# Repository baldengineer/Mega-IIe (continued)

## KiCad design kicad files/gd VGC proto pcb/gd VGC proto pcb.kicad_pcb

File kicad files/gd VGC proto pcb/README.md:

## gd VGC proto pcb
VGC = Video Graphics Controller

First board to be finished and the one with the least use for the final handheld. The VGC converts the RGB bitstream from the MEGA-II into an analog signal and then into NTSC.

The VGC also generates the 14 MHz clock from a 28 MHz oscilliator. (It is not clear yet which clocks the MEGA-II generates and which the VGC does.)

Runs off of +5V, -5V, and +12V. The 12V and -5V are used by the NTSC generation circuit.

## Rev1 Notes:
* Nothing... yet :)

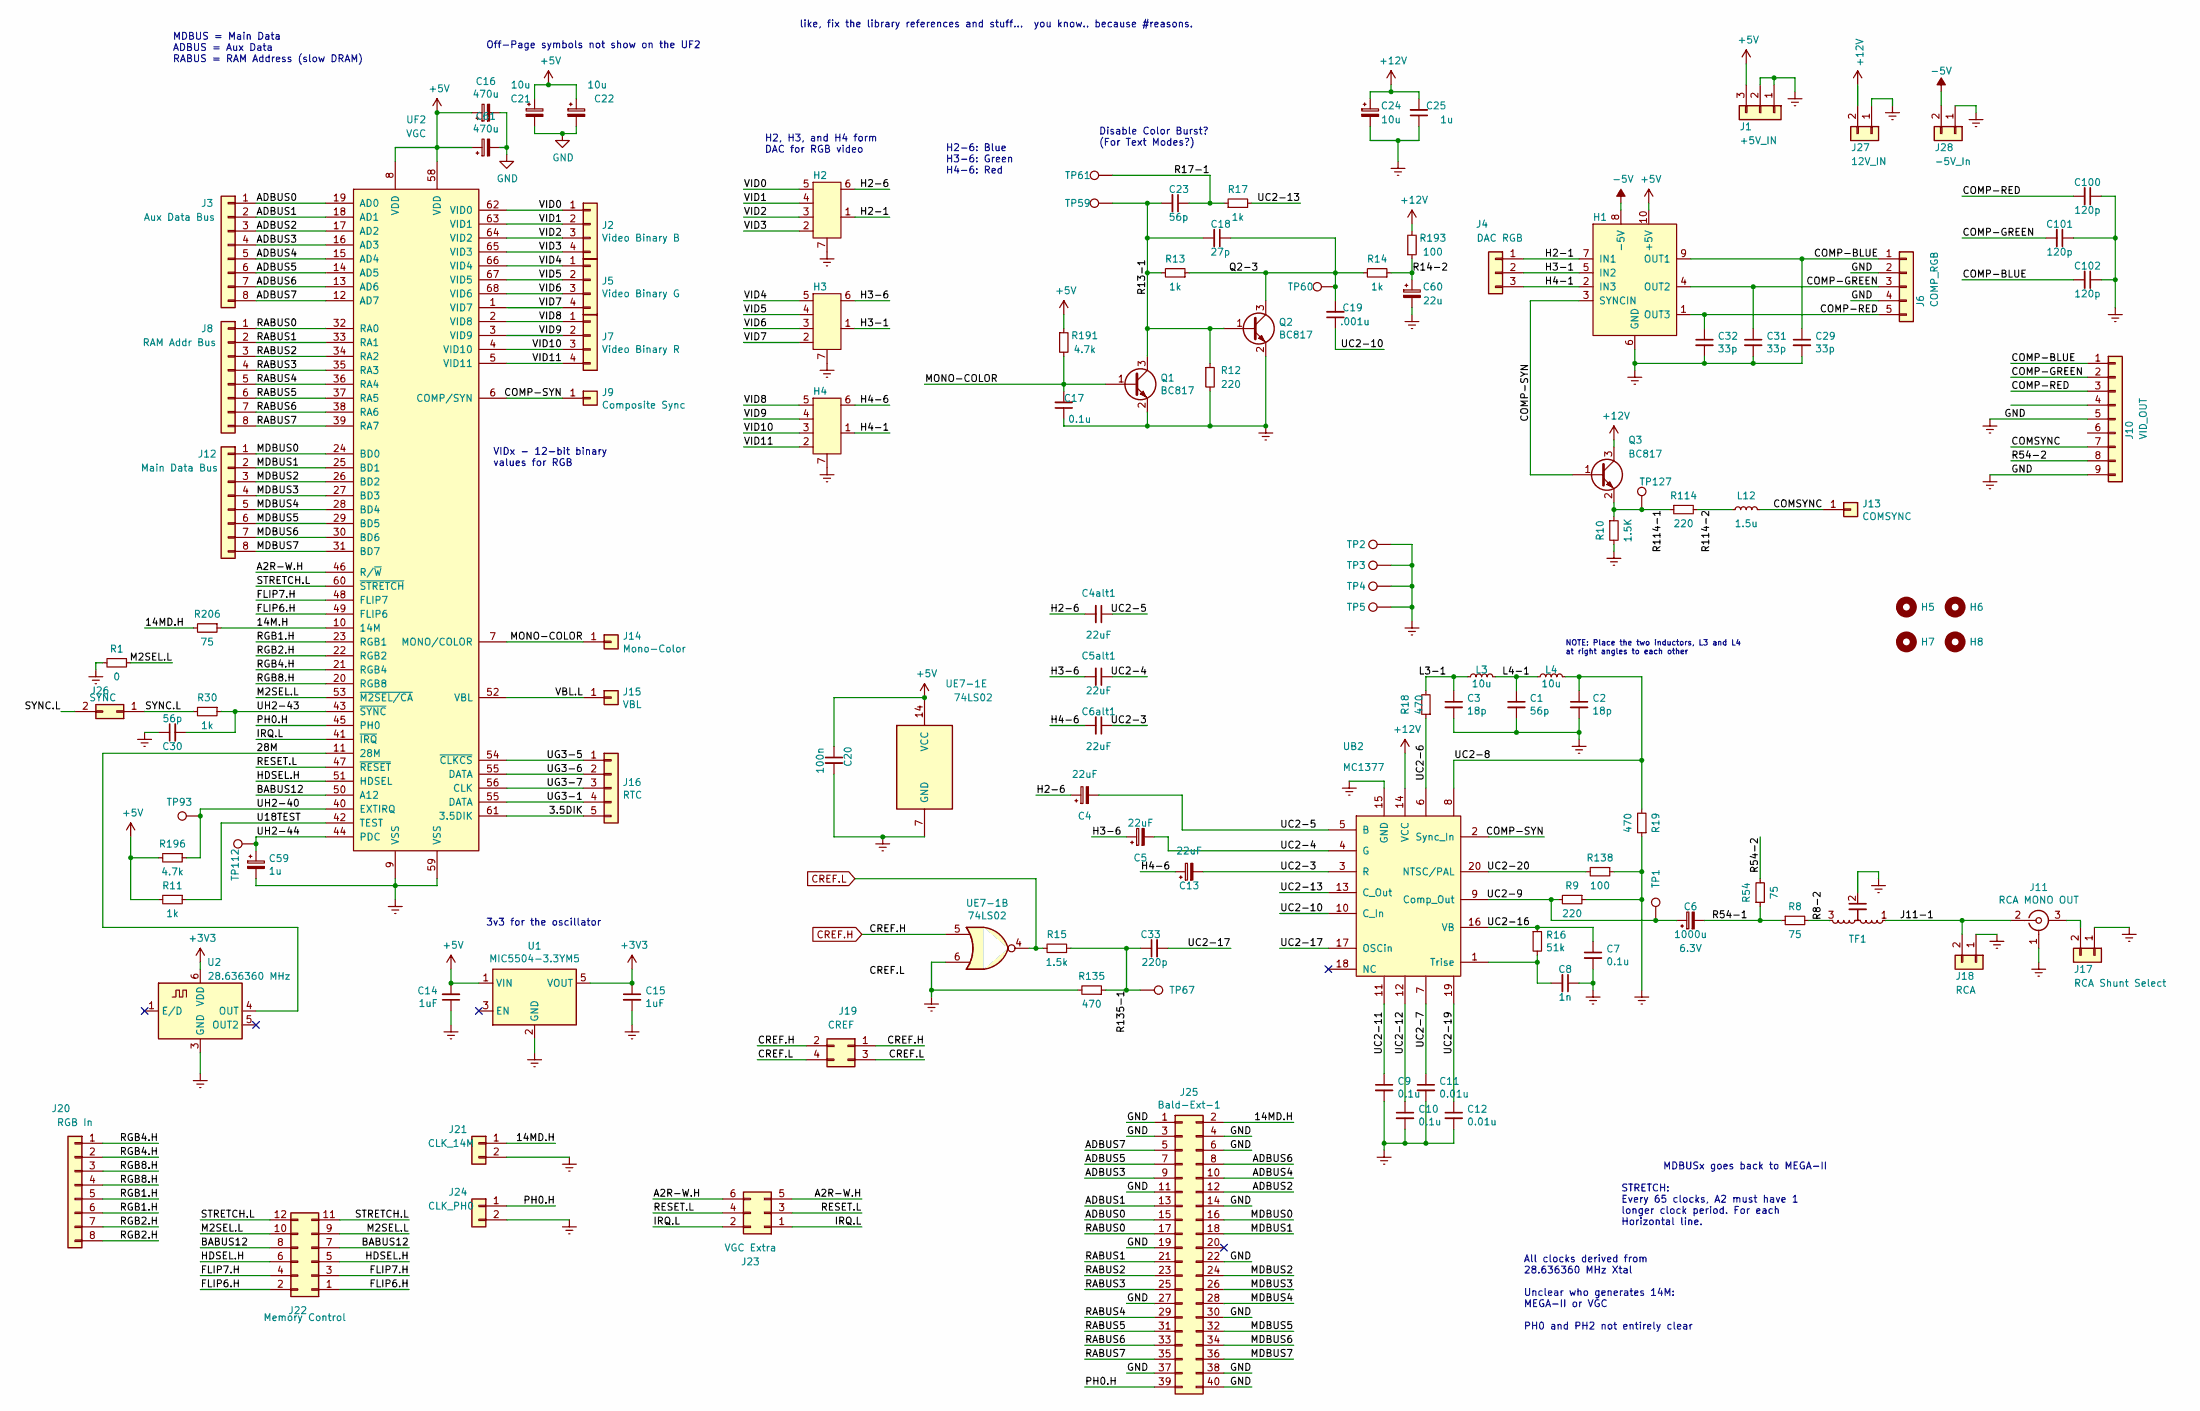
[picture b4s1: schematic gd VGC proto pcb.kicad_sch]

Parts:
C1, C23, C30: 56p; C_0805_2012Metric
C2, C3: 18p; C_0805_2012Metric
C4, C5, C13: 22uF; CP_Radial_D5.0mm_P2.00mm
C4alt1, C5alt1, C6alt1: 22uF; C_0805_2012Metric
C6: 1000u; CP_Radial_D10.0mm_P2.50mm; Voltage 6.3V
C7, C9, C10, C17: 0.1u; C_0805_2012Metric
C8: 1n; C_0805_2012Metric
C11, C12: 0.01u; C_0805_2012Metric
C14, C15: 1uF; C_0805_2012Metric
C16, C61: 470u; CP_Radial_D10.0mm_P2.50mm
C18: 27p; C_0805_2012Metric
C19: .001u; C_0805_2012Metric
C20: 100n; C_0805_2012Metric
C21, C22, C24: 10u; CP_Radial_D5.0mm_P2.50mm
C25, C59: 1u; C_0805_2012Metric
C29, C31, C32: 33p; C_0805_2012Metric
C33: 220p; C_0805_2012Metric
C60: 22u; CP_Radial_D5.0mm_P2.50mm
C100, C101, C102: 120p; C_0805_2012Metric
H1: Video_Sync; R_Array_SIP10
H2, H3, H4: VideoThingy; R_Array_SIP7
H5, H6, H7, H8: MountingHole; MountingHole_2.7mm_M2.5
J1: +5V_IN; PinHeader_1x03_P2.54mm_Vertical
J2: Video Binary B; PinHeader_1x04_P2.54mm_Vertical
J3: Aux Data Bus; PinHeader_1x08_P2.54mm_Vertical
J4: DAC RGB; PinHeader_1x03_P2.54mm_Vertical
J5: Video Binary G; PinHeader_1x04_P2.54mm_Vertical
J6: COMP_RGB; PinHeader_1x05_P2.54mm_Vertical
J7: Video Binary R; PinHeader_1x04_P2.54mm_Vertical
J8: RAM Addr Bus; PinHeader_1x08_P2.54mm_Vertical
J9: Composite Sync; PinHeader_1x01_P2.54mm_Vertical
J10: VID_OUT; PinHeader_1x09_P2.54mm_Vertical
J11: RCA MONO OUT; Jack_RCA_Switchcraft_PJRAN1X1UxxX; MPN PJRAN1X1U02AUX
J12: Main Data Bus; PinHeader_1x08_P2.54mm_Vertical
J13: COMSYNC; PinHeader_1x01_P2.54mm_Vertical
J14: Mono-Color; PinHeader_1x01_P2.54mm_Vertical
J15: VBL; PinHeader_1x01_P2.54mm_Vertical
J16: RTC; PinHeader_1x05_P2.54mm_Vertical
J17: RCA Shunt Select; PinHeader_1x02_P2.54mm_Vertical
J18: RCA; PinHeader_1x02_P2.54mm_Vertical
J19: CREF; PinHeader_2x02_P2.54mm_Vertical
J20: RGB In; PinHeader_1x08_P2.54mm_Vertical
J21: CLK_14M; PinHeader_1x02_P2.54mm_Vertical
J22: Memory Control; PinHeader_2x06_P2.54mm_Vertical
J23: VGC Extra; PinHeader_2x03_P2.54mm_Vertical
J24: CLK_PH0; PinHeader_1x02_P2.54mm_Vertical
J25: Bald-Ext-1; PinHeader_2x20_P2.54mm_Vertical
J26: SYNC; PinHeader_1x02_P2.54mm_Vertical
J27: 12V_IN; PinHeader_1x02_P2.54mm_Vertical
J28: -5V_In; PinHeader_1x02_P2.54mm_Vertical
L3, L4: 10u; L_Axial_L6.6mm_D2.7mm_P10.16mm_Horizontal_Vishay_IM-2
L12: 1.5u; L_Axial_L6.6mm_D2.7mm_P10.16mm_Horizontal_Vishay_IM-2
Q1, Q2, Q3: BC817; SOT-23
R1: 0; R_0805_2012Metric
R8, R54, R206: 75; R_0805_2012Metric
R9, R12, R114: 220; R_0805_2012Metric
R10: 1.5K; R_0805_2012Metric
R11, R13, R14, R17, R30: 1k; R_0805_2012Metric
R15: 1.5k; R_0805_2012Metric
R16: 51k; R_0805_2012Metric
R18, R19, R135: 470; R_0805_2012Metric
R138, R193: 100; R_0805_2012Metric
R191, R196: 4.7k; R_0805_2012Metric
TF1: CapacitiveTransformer; TO-92
TP1, TP2, TP3, TP4, TP5, TP59, TP60, TP61, TP67, TP93, TP112, TP127: TestPoint; Harwin-S1751-46-Test-Point
U1: MIC5504-3.3YM5; SOT-23-5
U2: 28.636360 MHz; Oscillator_SMD_IDT_JU6-6_7.0x5.0mm_P2.54mm
UB2: MC1377; DIP-20_W7.62mm_Socket
UE7-1: 74LS02; SOIC-14_3.9x8.7mm_P1.27mm
UF2: VGC; PLCC-68_THT-Socket

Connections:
+3V3: C15.1, U1.5 (VOUT), U2.6 (VDD)
+5V: C14.2, C16.1, C20.1, C21.1, C22.1, C61.1, H1.10 (+5V), J1.3, R11.2, R191.1, R196.2, U1.1 (VIN), UE7-1.14 (VCC), UF2.8 (VDD), UF2.58 (VDD)
+12V: C24.1, C25.2, J27.2, Q3.3 (C), R193.2, UB2.14 (VCC)
-5V: H1.8 (-5V), J28.2
/3.5DIK: J16.5, UF2.61 (3.5DIK)
/14M.H: R206.1, UF2.10 (14M)
/14MD.H: J21.1, J25.2, R206.2
/28M: U2.4 (OUT), UF2.11 (28M)
/A2R-W.H: J23.5, J23.6, UF2.46 (R/~W)
/ADBUS0: J3.1, J25.15, UF2.19 (AD0)
/ADBUS1: J3.2, J25.13, UF2.18 (AD1)
/ADBUS2: J3.3, J25.12, UF2.17 (AD2)
/ADBUS3: J3.4, J25.9, UF2.16 (AD3)
/ADBUS4: J3.5, J25.10, UF2.15 (AD4)
/ADBUS5: J3.6, J25.7, UF2.14 (AD5)
/ADBUS6: J3.7, J25.8, UF2.13 (AD6)
/ADBUS7: J3.8, J25.5, UF2.12 (AD7)
/BABUS12: J22.7, J22.8, UF2.50 (A12)
/COMP-BLUE: C29.1, C102.2, H1.9 (OUT1), J6.1, J10.1
/COMP-GREEN: C31.1, C101.2, H1.4 (OUT2), J6.3, J10.2
/COMP-RED: C32.1, C100.2, H1.1 (OUT3), J6.5, J10.3
/COMP-SYN: H1.3 (SYNCIN), J9.1, Q3.1 (B), UB2.2 (Sync_In), UF2.6 (COMP/SYN)
/COMSYNC: J10.7, J13.1, L12.2
/FLIP6.H: J22.1, J22.2, UF2.49 (FLIP6)
/FLIP7.H: J22.3, J22.4, UF2.48 (FLIP7)
/H2-1: H1.7 (IN1), H2.1, J4.1
/H2-6: C4.1, C4alt1.2, H2.6
/H3-1: H1.5 (IN2), H3.1, J4.2
/H3-6: C5.1, C5alt1.2, H3.6
/H4-1: H1.2 (IN3), H4.1, J4.3
/H4-6: C6alt1.2, C13.1, H4.6
/HDSEL.H: J22.5, J22.6, UF2.51 (HDSEL)
/IRQ.L: J23.1, J23.2, UF2.41 (~IRQ)
/J11-1: J11.2 (In), J18.2, TF1.1
/L3-1: C3.1, L3.1, R18.2
/L4-1: C1.1, L3.2, L4.1
/M2SEL.L: J22.9, J22.10, R1.1, UF2.53 (~M2SEL/CA)
/MDBUS0: J12.1, J25.16, UF2.24 (BD0)
/MDBUS1: J12.2, J25.18, UF2.25 (BD1)
/MDBUS2: J12.3, J25.24, UF2.26 (BD2)
/MDBUS3: J12.4, J25.26, UF2.27 (BD3)
/MDBUS4: J12.5, J25.28, UF2.28 (BD4)
/MDBUS5: J12.6, J25.32, UF2.29 (BD5)
/MDBUS6: J12.7, J25.34, UF2.30 (BD6)
/MDBUS7: J12.8, J25.36, UF2.31 (BD7)
/MONO-COLOR: C17.2, J14.1, Q1.1 (B), R191.2, UF2.7 (MONO/COLOR)
/PH0.H: J24.1, J25.39, UF2.45 (PH0)
/Q2-3: C18.1, C19.2, Q2.3 (C), R13.1, R14.2, TP60.1
/R8-2: R8.2, TF1.3
/R13-1: C18.2, C23.2, Q1.3 (C), Q2.1 (B), R12.1, R13.2, TP59.1
/R14-2: C60.1, R14.1, R193.1
/R17-1: C23.1, R17.1, TP61.1
/R54-1: C6.2, R8.1, R54.1
/R54-2: J10.8, R54.2
/R114-1: Q3.2 (E), R10.1, R114.1, TP127.1
/R114-2: L12.1, R114.2
/R135-1: C33.1, R15.1, R135.1, TP67.1
/RABUS0: J8.1, J25.17, UF2.32 (RA0)
/RABUS1: J8.2, J25.21, UF2.33 (RA1)
/RABUS2: J8.3, J25.23, UF2.34 (RA2)
/RABUS3: J8.4, J25.25, UF2.35 (RA3)
/RABUS4: J8.5, J25.29, UF2.36 (RA4)
/RABUS5: J8.6, J25.31, UF2.37 (RA5)
/RABUS6: J8.7, J25.33, UF2.38 (RA6)
/RABUS7: J8.8, J25.35, UF2.39 (RA7)
/RESET.L: J23.3, J23.4, UF2.47 (~RESET)
/RGB1.H: J20.5, J20.6, UF2.23 (RGB1)
/RGB2.H: J20.7, J20.8, UF2.22 (RGB2)
/RGB4.H: J20.1, J20.2, UF2.21 (RGB4)
/RGB8.H: J20.3, J20.4, UF2.20 (RGB8)
/STRETCH.L: J22.11, J22.12, UF2.60 (~STRETCH)
/SYNC.L: J26.1, J26.2, R30.2
/U18TEST: R11.1, UF2.42 (TEST)
/UC2-3: C6alt1.1, C13.2, UB2.3 (R)
/UC2-4: C5.2, C5alt1.1, UB2.4 (G)
/UC2-5: C4.2, C4alt1.1, UB2.5 (B)
/UC2-6: R18.1, UB2.6
/UC2-7: C11.1, UB2.7
/UC2-8: C2.1, L4.2, R19.2, UB2.8
/UC2-9: C6.1, R9.2, TP1.1, UB2.9 (Comp_Out)
/UC2-10: C19.1, UB2.10 (C_In)
/UC2-11: C9.1, UB2.11
/UC2-12: C10.1, UB2.12
/UC2-13: R17.2, UB2.13 (C_Out)
/UC2-16: C7.1, R16.1, UB2.16 (VB)
/UC2-17: C33.2, UB2.17 (OSCin)
/UC2-19: C12.1, UB2.19
/UC2-20: R138.2, UB2.20 (NTSC/PAL)
/UG3-5: J16.1, UF2.54 (~CLKCS)
/UG3-7: J16.3, UF2.56 (CLK)
/UH2-40: R196.1, TP93.1, UF2.40 (EXTIRQ)
/UH2-43: C30.2, R30.1, UF2.43 (~SYNC)
/UH2-44: C59.1, TP112.1, UF2.44 (PDC)
/VBL.L: J15.1, UF2.52 (VBL)
/VID0: H2.5, J2.1, UF2.62 (VID0)
/VID1: H2.4, J2.2, UF2.63 (VID1)
/VID2: H2.3, J2.3, UF2.64 (VID2)
/VID3: H2.2, J2.4, UF2.65 (VID3)
/VID4: H3.5, J5.1, UF2.66 (VID4)
/VID5: H3.4, J5.2, UF2.67 (VID5)
/VID6: H3.3, J5.3, UF2.68 (VID6)
/VID7: H3.2, J5.4, UF2.1 (VID7)
/VID8: H4.5, J7.1, UF2.2 (VID8)
/VID9: H4.4, J7.2, UF2.3 (VID9)
/VID10: H4.3, J7.3, UF2.4 (VID10)
/VID11: H4.2, J7.4, UF2.5 (VID11)
CREF.H: J19.1, J19.2, UE7-1.5
CREF.L: J19.3, J19.4, R15.2, UE7-1.4
GND: C1.2, C2.2, C3.2, C7.2, C8.1, C9.2, C10.2, C11.2, C12.2, C14.1, C15.2, C16.2, C17.1, C20.2, C21.2, C22.2, C24.2, C25.1, C29.2, C30.1, C31.2, C32.2, C59.2, C60.2, C61.2, C100.1, C101.1, C102.1, H1.6 (GND), H2.7, H3.7, H4.7, J1.1, J1.2, J6.2, J6.4, J10.5, J10.9, J11.1 (Ext), J17.1, J18.1, J21.2, J24.2, J25.1, J25.3, J25.4, J25.6, J25.11, J25.14, J25.19, J25.22, J25.27, J25.30, J25.37, J25.38, J25.40, J27.1, J28.1, Q1.2 (E), Q2.2 (E), R1.2, R9.1, R10.2, R12.2, R19.1, R135.2, R138.1, TF1.2, TP2.1, TP3.1, TP4.1, TP5.1, U1.2 (GND), U2.3 (GND), UB2.15 (GND), UE7-1.6, UE7-1.7 (GND), UF2.9 (VSS), UF2.59 (VSS)
unnamed: C8.2, R16.2, UB2.1 (Trise)
unnamed: J11.3, J17.2

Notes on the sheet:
MDBUSx goes back to MEGA-II
MDBUS = Main Data ADBUS = Aux Data RABUS = RAM Address (slow DRAM)
Off-Page symbols not show on the UF2
H2, H3, and H4 form DAC for RGB video
Disable Color Burst? (For Text Modes?)
3v3 for the oscillator
H2-6: Blue H3-6: Green H4-6: Red
VIDx - 12-bit binary values for RGB
All clocks derived from 28.636360 MHz Xtal Unclear who generates 14M: MEGA-II or VGC PH0 and PH2 not entirely clear
STRETCH: Every 65 clocks, A2 must have 1 longer clock period. For each Horizontal line.
like, fix the library references and stuff... you know.. because #reasons.
NOTE: Place the two inductors, L3 and L4 at right angles to each other

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
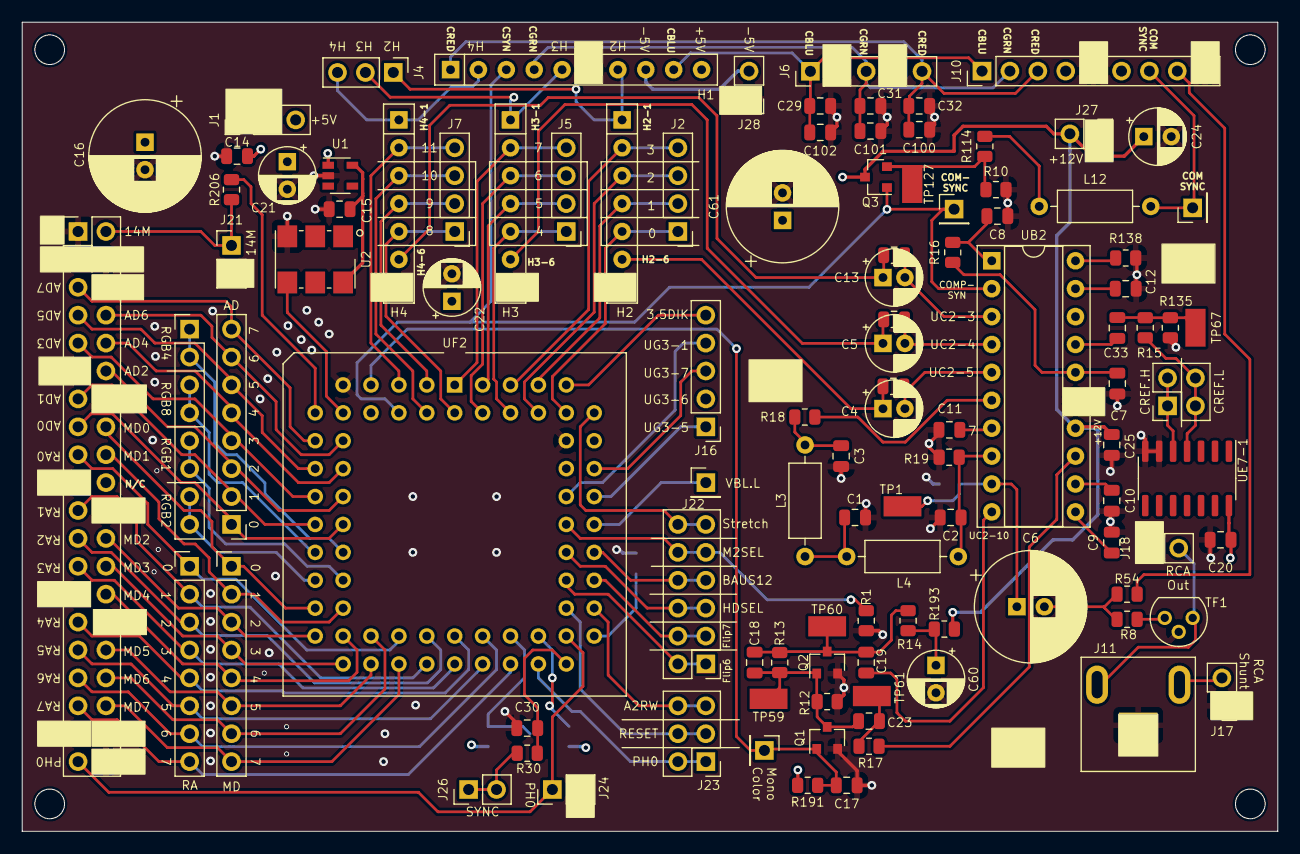
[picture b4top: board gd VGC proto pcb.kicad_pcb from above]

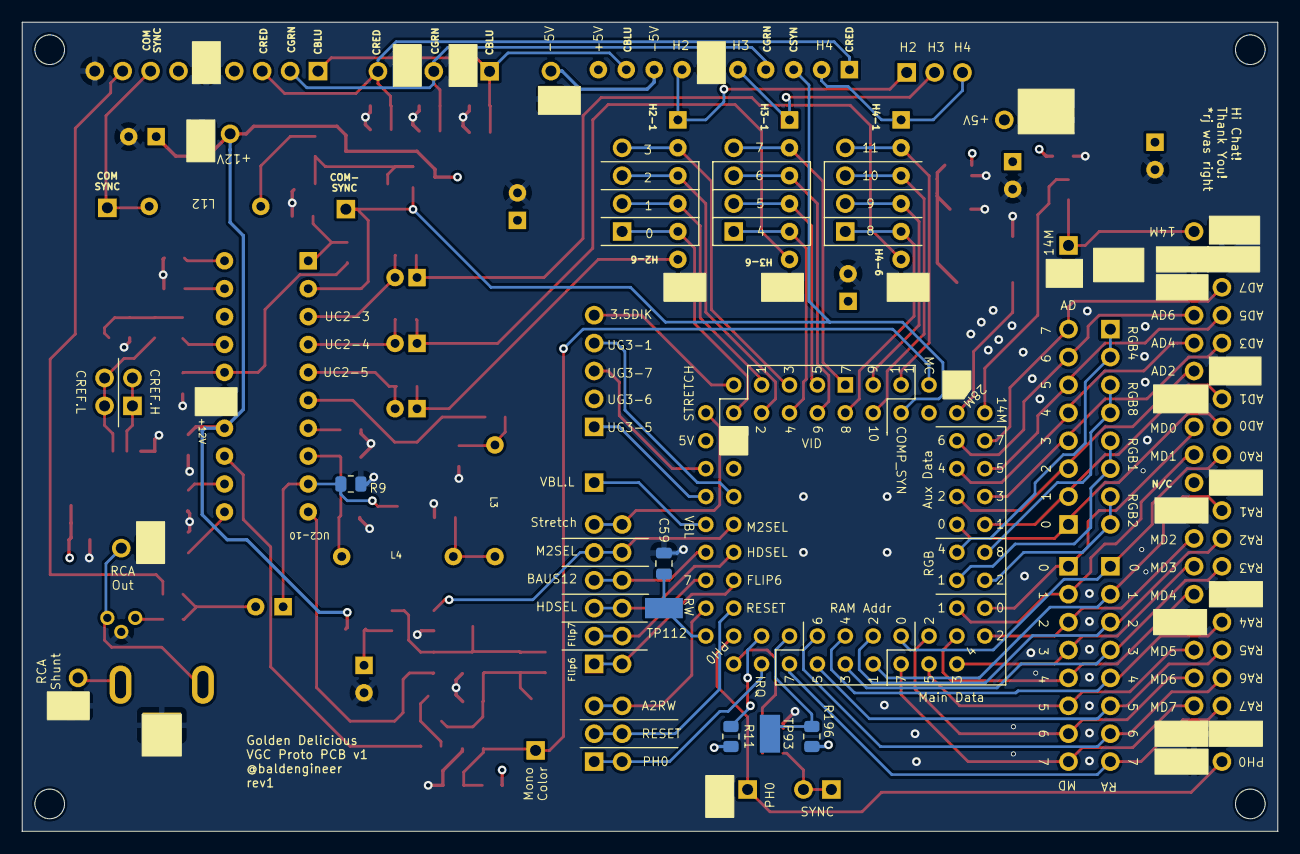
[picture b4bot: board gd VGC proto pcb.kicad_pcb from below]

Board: 4 copper layers, 114.3 x 73.7 mm, 121 parts (7 on the bottom side), 112 nets.

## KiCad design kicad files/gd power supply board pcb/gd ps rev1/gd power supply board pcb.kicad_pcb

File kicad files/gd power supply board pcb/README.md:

Four-rail SMPS for the Mega IIe. 

* Always-on 5V supply for the RP2040s and USB
* Switchable 5V for MEGA and other 5V Logic
* Switchable +12/-12V for disk drive and slot

Each 5V supply is designed for >1 Amp. The 12V supply was intended to provide at least 1 Amp. In rev1 testing it *could* provide 1 amp, but only for about 2 minutes. It's steady state max was around 750 mA. 

The -12V supply can only provide a few hundred milliamps. However, in my testing other the analog video circuit used it. At most, it would draw 50 mA but usually sat around 10 mA.

The rev1 design suffered from severe conducted ripple from the 5V switchers. So the rev2 re-design is a 4-layer board with significant ground shielding of input and output rails.

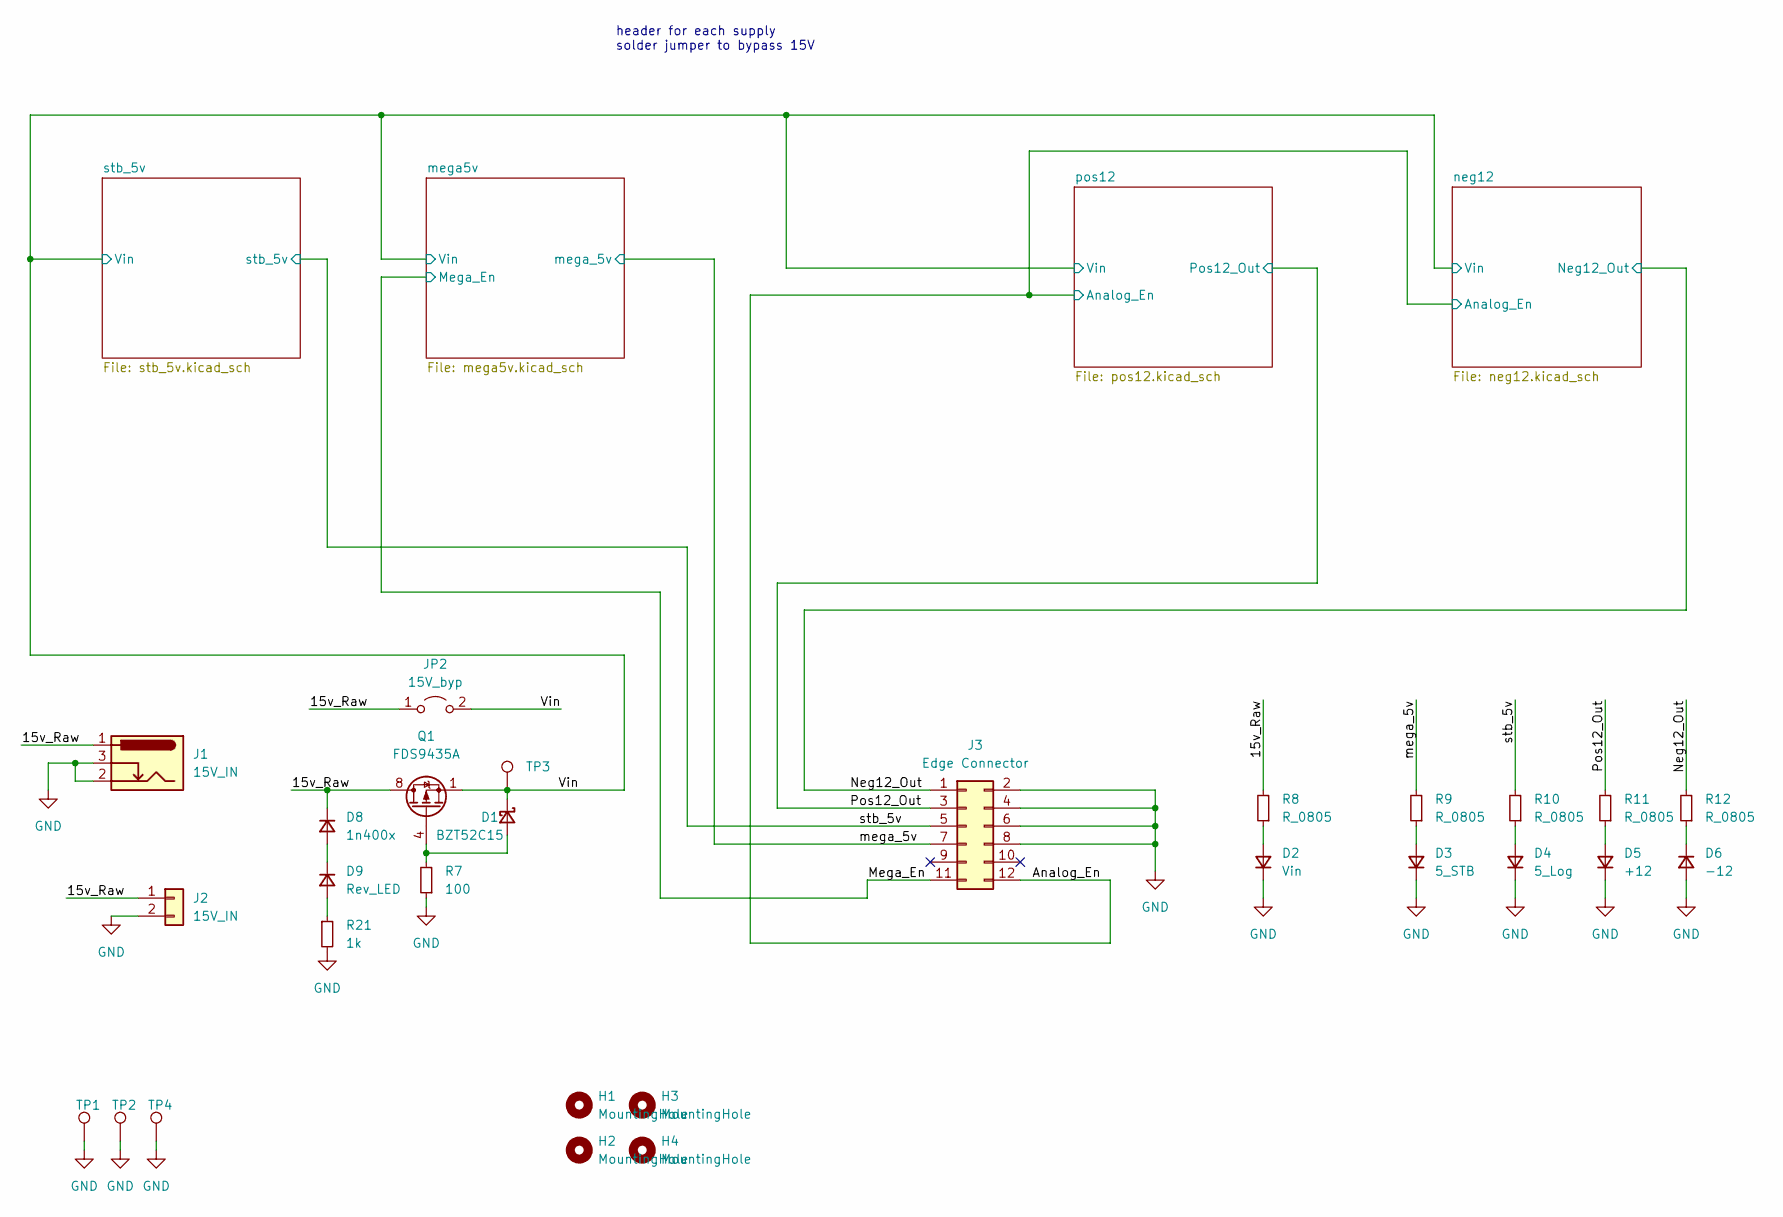
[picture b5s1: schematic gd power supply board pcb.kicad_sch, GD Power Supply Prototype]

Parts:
D1: BZT52C15; D_SOD-123
D2: Vin; LED_1206_3216Metric
D3: 5_STB; LED_1206_3216Metric
D4: 5_Log; LED_1206_3216Metric
D5: +12; LED_1206_3216Metric
D6: -12; LED_1206_3216Metric
D8: 1n400x; D_SMA
D9: Rev_LED; LED_1206_3216Metric
H1, H2, H3, H4: MountingHole; MountingHole_2.2mm_M2
J1: 15V_IN; BarrelJack_Horizontal
J2: 15V_IN; PinHeader_1x02_P2.54mm_Vertical
J3: Edge Connector; 12pos-edge-2.54mm
JP2: 15V_byp; SolderJumper-2_P1.3mm_Open_TrianglePad1.0x1.5mm
Q1: FDS9435A; SOIC-8_3.9x4.9mm_P1.27mm
R7: 100; R_0805_2012Metric
R8, R9, R10, R11, R12: R_0805; R_0805_2012Metric
R21: 1k; R_0805_2012Metric
TP1, TP2, TP3, TP4: TestPoint_Harwin; Harwin-S1751-46-Test-Point

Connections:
/15v_Raw: D8.1 (K), J1.1, J2.1, JP2.1 (A), Q1.5 (D), Q1.6 (D), Q1.7 (D), Q1.8 (D), R8.2
/Analog_En: J3.12; also elsewhere on the board
/Mega_En: J3.11; also elsewhere on the board
/Neg12_Out: J3.1, R12.2; also elsewhere on the board
/Pos12_Out: J3.3, R11.2; also elsewhere on the board
/Vin: D1.1 (K), JP2.2 (B), Q1.1 (S), Q1.2 (S), Q1.3 (S), TP3.1; also elsewhere on the board
/mega_5v: J3.7, R9.2; also elsewhere on the board
/stb_5v: J3.5, R10.2; also elsewhere on the board
GND: D2.1 (K), D3.1 (K), D4.1 (K), D5.1 (K), D6.2 (A), J1.2, J1.3, J2.2, J3.2, J3.4, J3.6, J3.8, R7.1, R21.2, TP1.1, TP2.1, TP4.1; also elsewhere on the board
unnamed: D1.2 (A), Q1.4 (G), R7.2
unnamed: D2.2 (A), R8.1
unnamed: D3.2 (A), R9.1
unnamed: D4.2 (A), R10.1
unnamed: D5.2 (A), R11.1
unnamed: D6.1 (K), R12.1
unnamed: D8.2 (A), D9.1 (K)
unnamed: D9.2 (A), R21.1

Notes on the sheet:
header for each supply solder jumper to bypass 15V

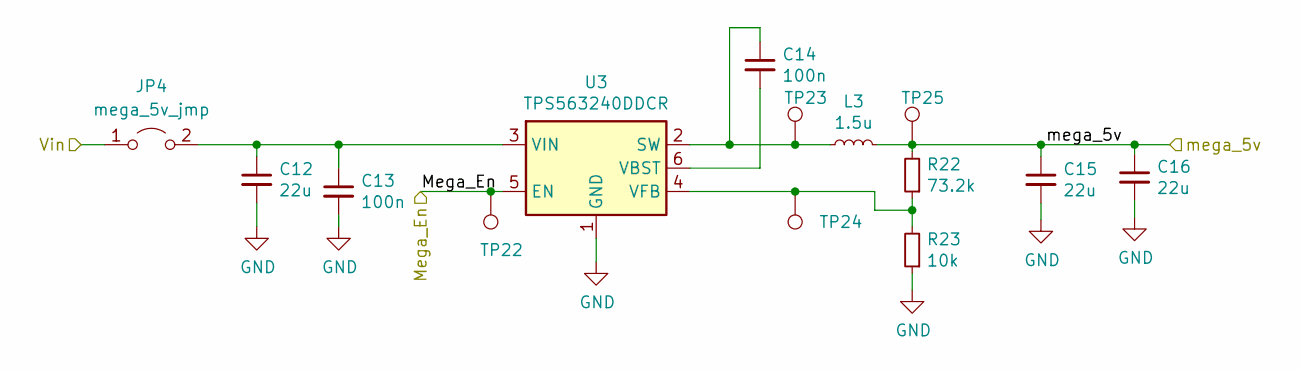
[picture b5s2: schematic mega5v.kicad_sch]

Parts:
C12, C15, C16: 22u; C_0805_2012Metric
C13, C14: 100n; C_0603_1608Metric
JP4: mega_5v_jmp; SolderJumper-2_P1.3mm_Open_TrianglePad1.0x1.5mm
L3: 1.5u; L_Bourns_SRP5030T
R22: 73.2k; R_0603_1608Metric
R23: 10k; R_0603_1608Metric
TP22, TP23, TP24, TP25: TestPoint_Harwin; Harwin-S1751-46-Test-Point
U3: TPS563240DDCR; SOT-23-6

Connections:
/Mega_En: TP22.1, U3.5 (EN); also elsewhere on the board
/Vin: JP4.1 (A); also elsewhere on the board
/mega_5v: C15.1, C16.1, L3.2, R22.2, TP25.1; also elsewhere on the board
GND: C12.2, C13.2, C15.2, C16.2, R23.1, U3.1 (GND); also elsewhere on the board
unnamed: C12.1, C13.1, JP4.2 (B), U3.3 (VIN)
unnamed: C14.1, L3.1, TP23.1, U3.2 (SW)
unnamed: C14.2, U3.6 (VBST)
unnamed: R22.1, R23.2, TP24.1, U3.4 (VFB)

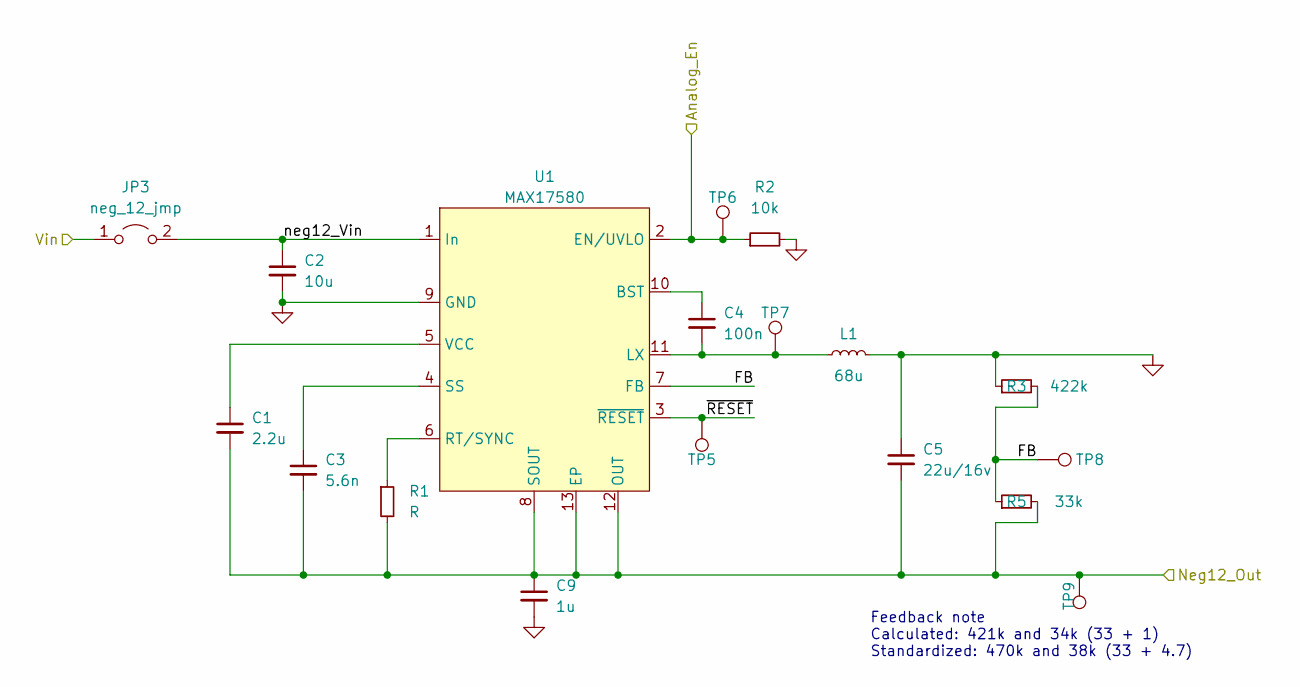
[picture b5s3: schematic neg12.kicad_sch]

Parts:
C1: 2.2u; C_0603_1608Metric
C2: 10u; C_0805_2012Metric
C3: 5.6n; C_0603_1608Metric
C4: 100n; C_0603_1608Metric
C5: 22u/16v; C_0805_2012Metric
C9: 1u; C_0805_2012Metric
JP3: neg_12_jmp; SolderJumper-2_P1.3mm_Open_TrianglePad1.0x1.5mm
L1: 68u; L_Taiyo-Yuden_NR-80xx
R1: R; R_0402_1005Metric
R2: 10k; R_0805_2012Metric
R3: 422k; R_0805_2012Metric
R5: 33k; R_0805_2012Metric
TP5, TP6, TP8: TestPoint_Harwin; TestPoint_Pad_1.0x1.0mm
TP7, TP9: TestPoint_Harwin; Harwin-S1751-46-Test-Point
U1: MAX17580; DFN-12-1EP_3x3mm_P0.5mm_EP2.05x2.86mm

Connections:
/Analog_En: R2.1, TP6.1, U1.2 (EN/UVLO); also elsewhere on the board
/Neg12_Out: C1.2, C3.2, C5.2, C9.1, R1.2, R5.2, TP9.1, U1.8 (SOUT), U1.12 (OUT), U1.13 (EP); also elsewhere on the board
/Vin: JP3.1 (A); also elsewhere on the board
/neg12/FB: R3.2, R5.1, TP8.1, U1.7 (FB)
/neg12/neg12_Vin: C2.1, JP3.2 (B), U1.1 (In)
/neg12/~RESET: TP5.1, U1.3 (~RESET)
GND: C2.2, C5.1, C9.2, L1.2, R2.2, R3.1, U1.9 (GND); also elsewhere on the board
unnamed: C1.1, U1.5 (VCC)
unnamed: C3.1, U1.4 (SS)
unnamed: C4.1, U1.10 (BST)
unnamed: C4.2, L1.1, TP7.1, U1.11 (LX)
unnamed: R1.1, U1.6 (RT/SYNC)

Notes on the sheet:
Feedback note Calculated: 421k and 34k (33 + 1) Standardized: 470k and 38k (33 + 4.7)

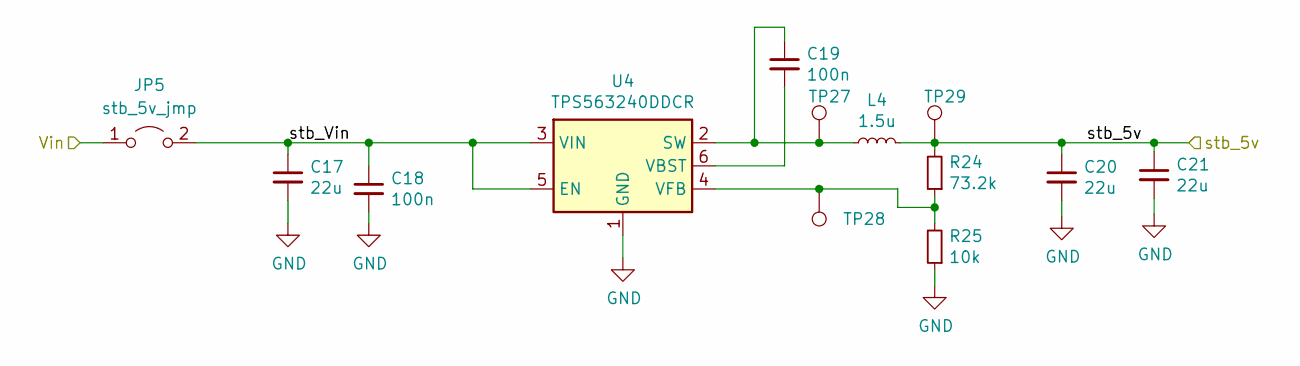
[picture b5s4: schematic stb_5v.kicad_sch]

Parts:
C17, C20, C21: 22u; C_0805_2012Metric
C18, C19: 100n; C_0603_1608Metric
JP5: stb_5v_jmp; SolderJumper-2_P1.3mm_Open_TrianglePad1.0x1.5mm
L4: 1.5u; L_Bourns_SRP5030T
R24: 73.2k; R_0603_1608Metric
R25: 10k; R_0603_1608Metric
TP27, TP28, TP29: TestPoint_Harwin; Harwin-S1751-46-Test-Point
U4: TPS563240DDCR; SOT-23-6

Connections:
/Vin: JP5.1 (A); also elsewhere on the board
/stb_5v: C20.1, C21.1, L4.2, R24.2, TP29.1; also elsewhere on the board
/stb_5v/stb_Vin: C17.1, C18.1, JP5.2 (B), U4.3 (VIN), U4.5 (EN)
GND: C17.2, C18.2, C20.2, C21.2, R25.1, U4.1 (GND); also elsewhere on the board
unnamed: C19.1, L4.1, TP27.1, U4.2 (SW)
unnamed: C19.2, U4.6 (VBST)
unnamed: R24.1, R25.2, TP28.1, U4.4 (VFB)

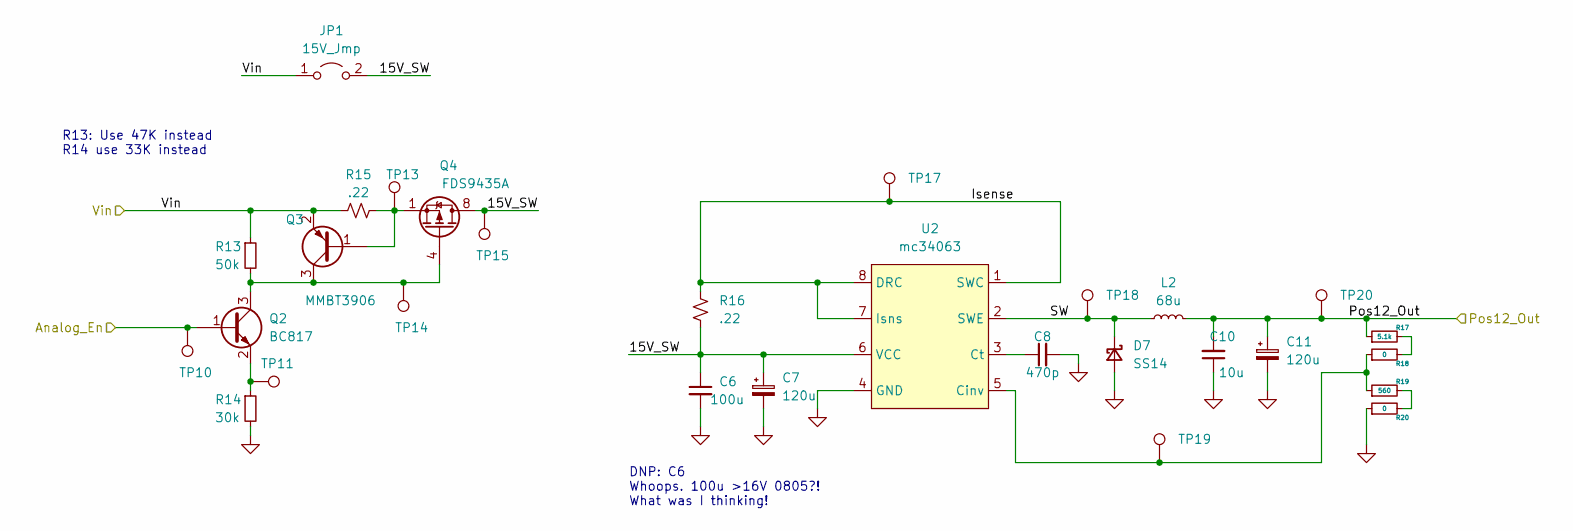
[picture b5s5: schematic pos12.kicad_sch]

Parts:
C6: 100u; C_0805_2012Metric
C7, C11: 120u; CP_Radial_D8.0mm_P3.80mm
C8: 470p; C_0603_1608Metric
C10: 10u; C_0805_2012Metric
D7: SS14; D_SMA
JP1: 15V_Jmp; SolderJumper-2_P1.3mm_Open_TrianglePad1.0x1.5mm
L2: 68u; L_Taiyo-Yuden_NR-80xx
Q2: BC817; SOT-23
Q3: MMBT3906; SOT-23
Q4: FDS9435A; SOIC-8_3.9x4.9mm_P1.27mm
R13: 50k; R_0805_2012Metric
R14: 30k; R_0805_2012Metric
R15, R16: .22; R_0805_2012Metric
R17, R20: 0; R_0805_2012Metric
R18: 5.1k; R_0805_2012Metric
R19: 560; R_0805_2012Metric
TP10, TP11, TP13, TP14, TP15, TP17, TP18, TP19, TP20: TestPoint_Harwin; Harwin-S1751-46-Test-Point
U2: mc34063; SOIC-8_3.9x4.9mm_P1.27mm

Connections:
/Analog_En: Q2.1 (B), TP10.1; also elsewhere on the board
/Pos12_Out: C10.2, C11.1, L2.2, R17.1, TP20.1; also elsewhere on the board
/Vin: JP1.1 (A), Q3.2 (E), R13.1, R15.1; also elsewhere on the board
/pos12/15V_SW: C6.1, C7.1, JP1.2 (B), Q4.5 (D), Q4.6 (D), Q4.7 (D), Q4.8 (D), R16.2, TP15.1, U2.6 (VCC)
/pos12/Isense: R16.1, TP17.1, U2.1 (SWC), U2.7 (Isns), U2.8 (DRC)
/pos12/SW: D7.1 (K), L2.1, TP18.1, U2.2 (SWE)
GND: C6.2, C7.2, C8.2, C10.1, C11.2, D7.2 (A), R14.2, R20.1, U2.4 (GND); also elsewhere on the board
unnamed: C8.1, U2.3 (Ct)
unnamed: Q2.2 (E), R14.1, TP11.1
unnamed: Q2.3 (C), Q3.3 (C), Q4.4 (G), R13.2, TP14.1
unnamed: Q3.1 (B), Q4.1 (S), Q4.2 (S), Q4.3 (S), R15.2, TP13.1
unnamed: R17.2, R18.2
unnamed: R18.1, R19.1, TP19.1, U2.5 (Cinv)
unnamed: R19.2, R20.2

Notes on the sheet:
DNP: C6 Whoops. 100u >16V 0805?! What was I thinking!
R13: Use 47K instead R14 use 33K instead

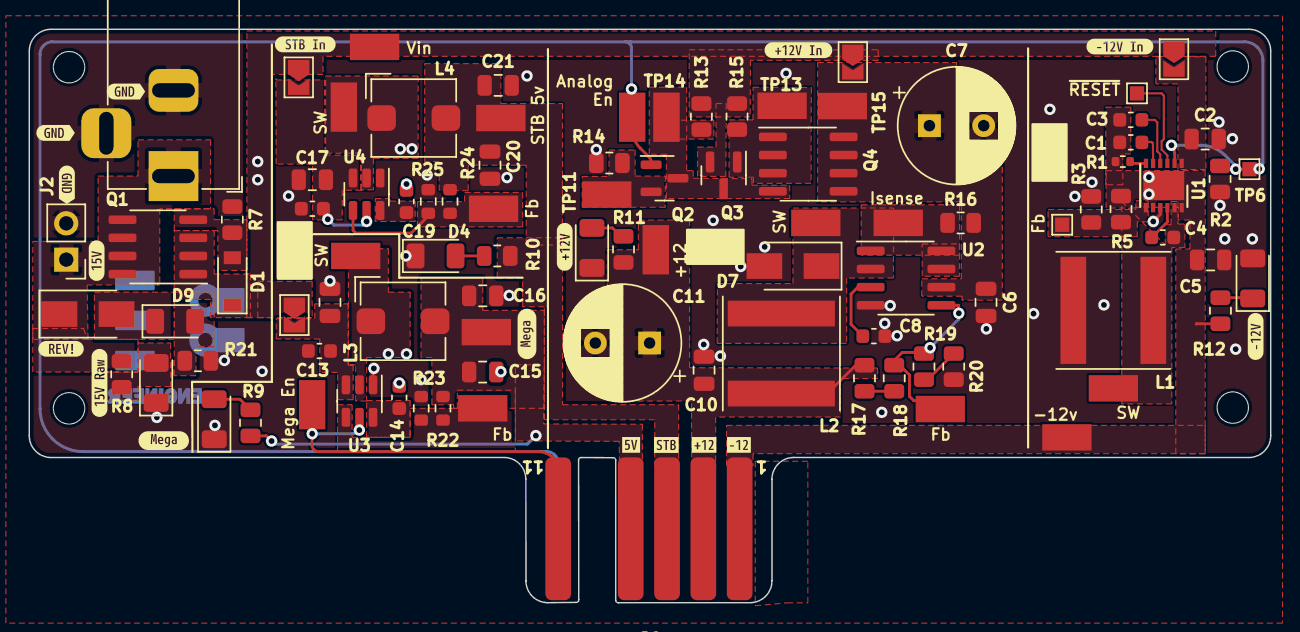
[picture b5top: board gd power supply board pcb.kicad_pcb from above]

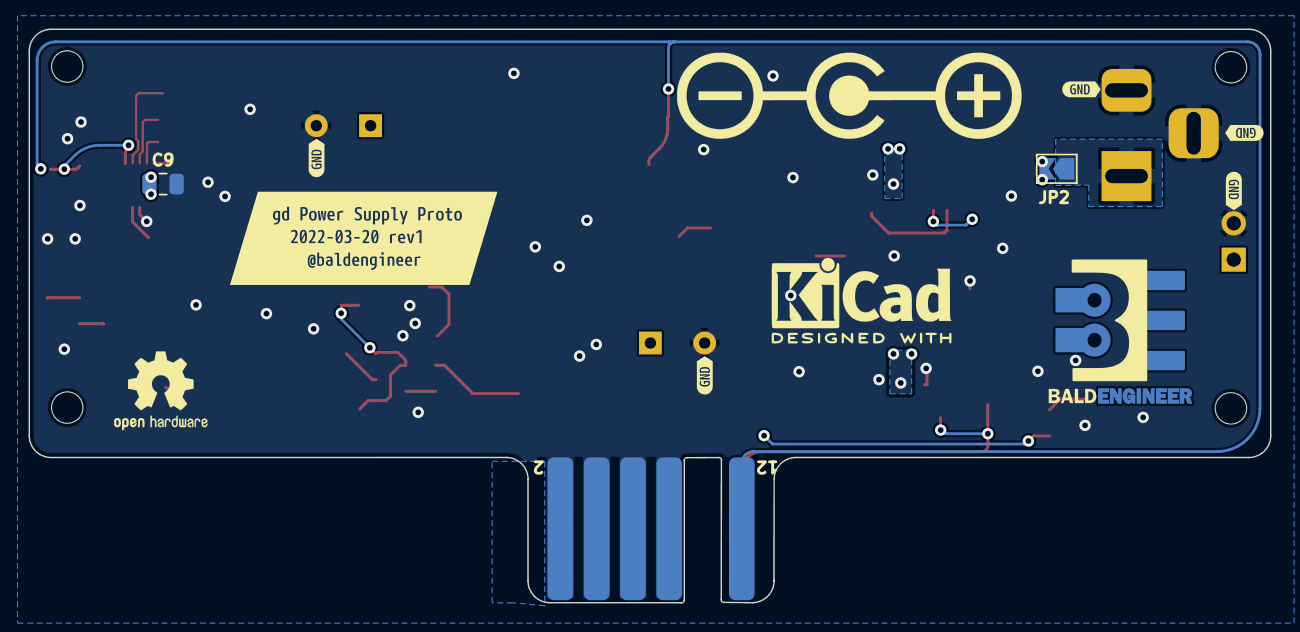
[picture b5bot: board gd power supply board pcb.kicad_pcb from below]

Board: 2 copper layers, 86.9 x 40.1 mm, 126 parts (9 on the bottom side), 43 nets.

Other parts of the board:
kibuzzard-62380C70: G***; kibuzzard-62380C70
kibuzzard-62380CC4: G***; kibuzzard-62380CC4
kibuzzard-62380CD9, kibuzzard-62380CD9#2: G***; kibuzzard-62380CD9
kibuzzard-62380D7E: G***; kibuzzard-62380D7E
kibuzzard-62380DAB: G***; kibuzzard-62380DAB
kibuzzard-62380E7D: G***; kibuzzard-62380E7D
kibuzzard-62380F2D: G***; kibuzzard-62380F2D
kibuzzard-62380F77: G***; kibuzzard-62380F77
kibuzzard-62380FA1: G***; kibuzzard-62380FA1
kibuzzard-62380FF5: G***; kibuzzard-62380FF5
kibuzzard-62388B6B: G***; kibuzzard-62388B6B
kibuzzard-6238101E: G***; kibuzzard-6238101E
kibuzzard-6238106E, kibuzzard-6238106E#2, kibuzzard-6238106E#3, kibuzzard-6238106E#4, kibuzzard-6238106E#5, kibuzzard-6238106E#6, kibuzzard-6238106E#7, kibuzzard-6238106E#8: G***; kibuzzard-6238106E
kibuzzard-62381000: G***; kibuzzard-62381000
kibuzzard-62381032: G***; kibuzzard-62381032
svg2mod: G***; BE10v2
